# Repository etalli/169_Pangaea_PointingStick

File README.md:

# Pointing stick extension for Pangaea keyboard

This pointing stick extenson is for Pangaea keyboard RI 1.2. It allows to use pointing stick module without wiring the modules.
Needs to replace with the original Pro Micro cover with this extension.

## history
2023/05/27 Orderd rev1.3 and wait for the PCB.

2023/10/15 Updated PCB design, not tested yet.

2023/11/5  Added pitctures.

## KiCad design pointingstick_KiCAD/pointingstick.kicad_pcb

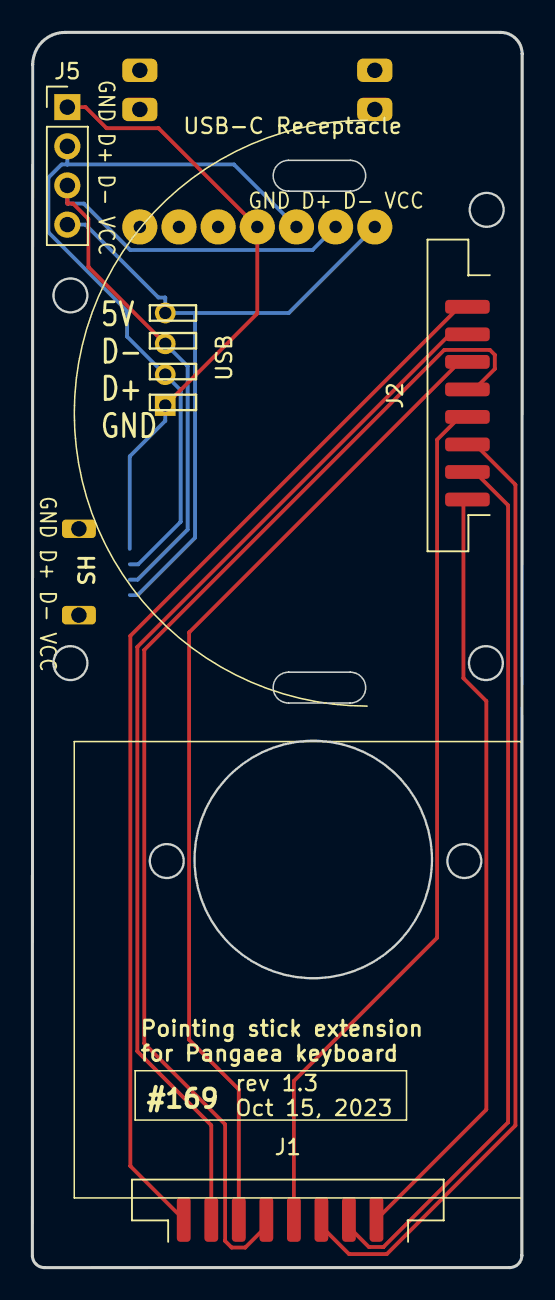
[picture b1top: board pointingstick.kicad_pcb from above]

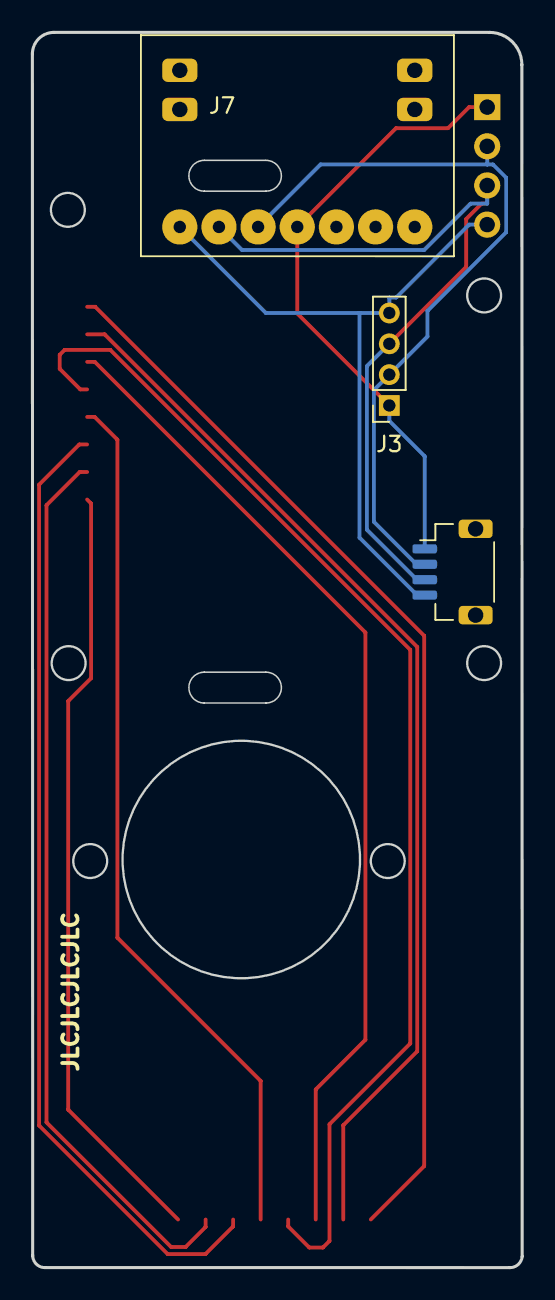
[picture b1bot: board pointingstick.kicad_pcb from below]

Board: 2 copper layers, 31.8 x 80.1 mm, 6 parts (3 on the bottom side), 12 nets.

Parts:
J1, J2: Conn_01x08_Socket; trackpoint-8pins-rev2
J3: Conn_01x04; PinSocket_1x04_P2.00mm_Vertical
J4: Conn_01x04; JST_SH_BM03B-SRSS-TB_1x04-1MP_P1.00mm_Vertical
J5: Conn_01x04; PinHeader_1x04_P2.54mm_Vertical
J7: USB_C_Receptacle_USB2.0; USB_C_Receptacle_AKIZUKIDENSHI

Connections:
D+: J3.2, J4.2, J5.2, J7.A6 (D+)
D-: J3.3, J4.3, J5.3, J7.A7 (D-)
GND: J3.1, J4.1, J5.1, J7.A1 (GND)
unnamed: J1.1, J2.8
unnamed: J1.2, J2.7
unnamed: J1.3, J2.6
unnamed: J1.4, J2.5
unnamed: J1.5, J2.4
unnamed: J1.6, J2.3
unnamed: J1.7, J2.2
unnamed: J1.8, J2.1
VCC: J3.4, J4.4, J5.4, J7.A4 (VBUS)

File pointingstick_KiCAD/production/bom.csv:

Designator,Footprint,Quantity,Value,LCSC Part #
"J1, J2",trackpoint-8pins-rev2,2,Conn_01x08_Socket,
J3,JST_SH_BM03B-SRSS-TB_1x04-1MP_P1.00mm_Vertical,1,Conn_01x04,
J4,PinSocket_1x04_P2.00mm_Vertical,1,Conn_01x04,
J5,PinHeader_1x04_P2.54mm_Vertical,1,Conn_01x04,
J6,USB_C_Receptacle_AKIZUKIDENSHI,1,USB_C_Receptacle_USB2.0,

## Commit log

2023-11-05 added pictures.
